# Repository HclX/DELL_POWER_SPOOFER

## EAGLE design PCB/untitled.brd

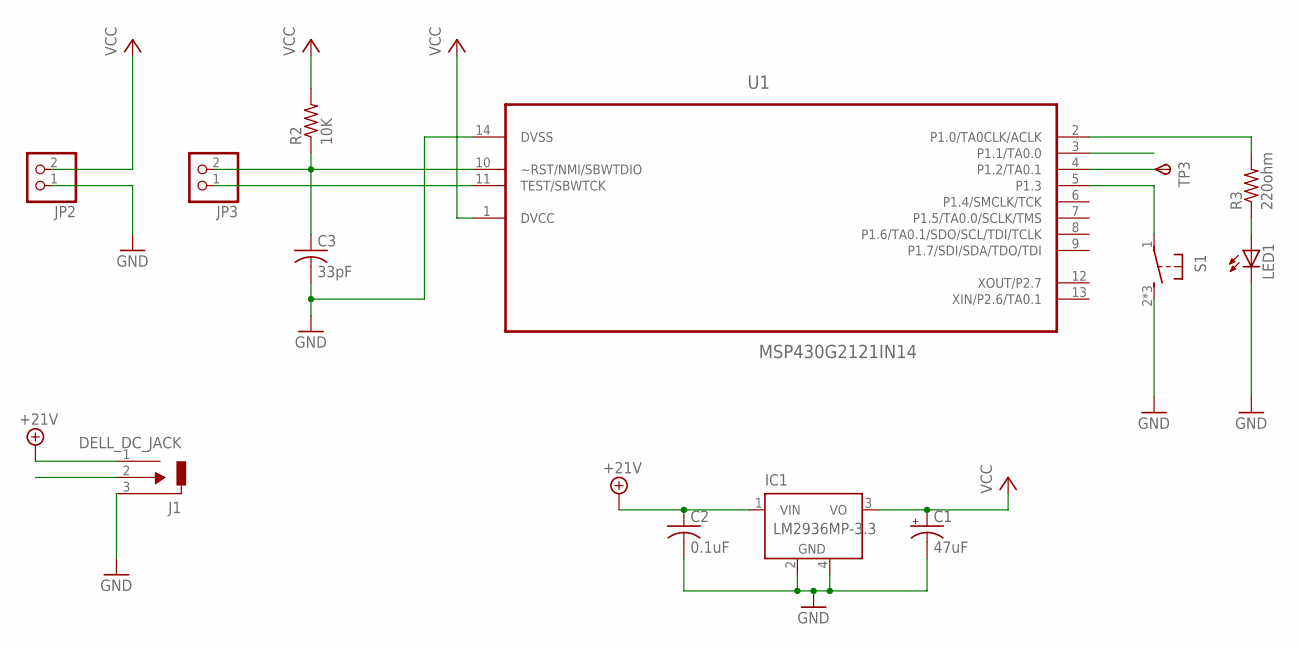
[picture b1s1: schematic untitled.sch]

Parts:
C1: 47uF; E2,5-5
C2: 0.1uF; C025-025X050
C3: 33pF; C025-025X050
IC1: LM2936MP-3.3; SOT223
J1: DELL_DC_JACK
JP2, JP3: PINHD-1X2; 1X02
LED1: LED3MM
R2: 10K; 0207/12
R3: 220ohm; 0207/12
S1: 31-XX; B3F-31XX
TP3: TPSPAD1-13; P1-13
U1: MSP430G2121IN14; DIP254P762X508-14

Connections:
+21V: C2.1, IC1.1 (VIN), J1.1 (VIN)
GND: C1.-, C2.2, C3.2, IC1.2 (GND), IC1.4 (GND), J1.3 (GND), JP2.1, LED1.K (C), S1.2 (S), S1.3 (S), S1.4 (S), U1.14 (DVSS)
unnamed: C3.1, JP3.2, R2.1, U1.10 (~RST/NMI/SBWTDIO)
unnamed: JP3.1, U1.11 (TEST/SBWTCK)
unnamed: R3.2, U1.2 (P1.0/TA0CLK/ACLK)
unnamed: LED1.A, R3.1
unnamed: TP3.TP, U1.4 (P1.2/TA0.1)
unnamed: S1.1, U1.5 (P1.3)
SIG: J1.2 (SIG), U1.3 (P1.1/TA0.0)
VCC: C1.+, IC1.3 (VO), JP2.2, R2.2, U1.1 (DVCC)

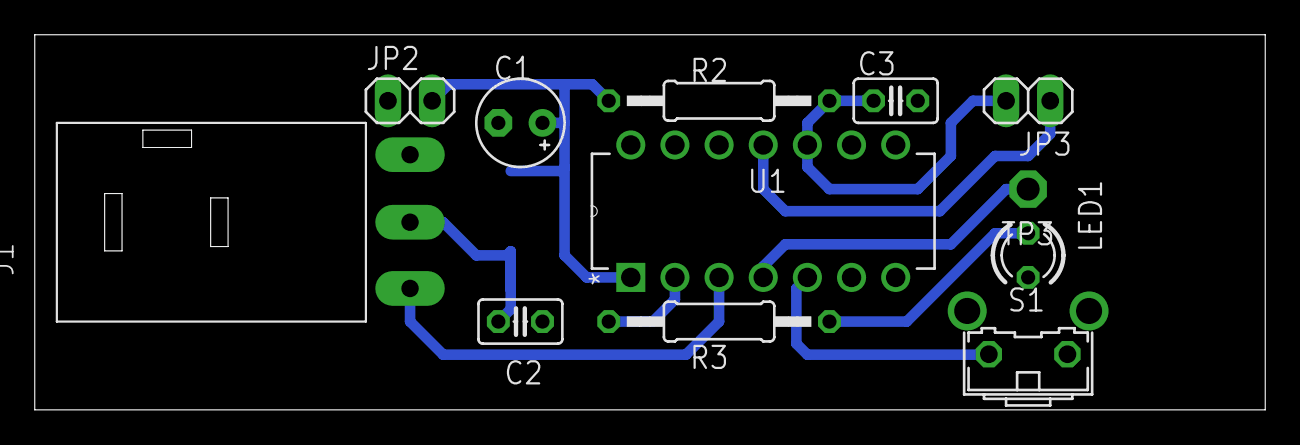
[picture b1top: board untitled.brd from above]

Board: 2 copper layers, 70.8 x 21.6 mm, 13 parts (1 on the bottom side), 10 nets.

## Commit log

2014-02-26 Separating from original repository
2014-02-26 making CCS happy
2014-02-26 printing out layout and schematic pdf files
2014-02-26 tweaking wattage info
